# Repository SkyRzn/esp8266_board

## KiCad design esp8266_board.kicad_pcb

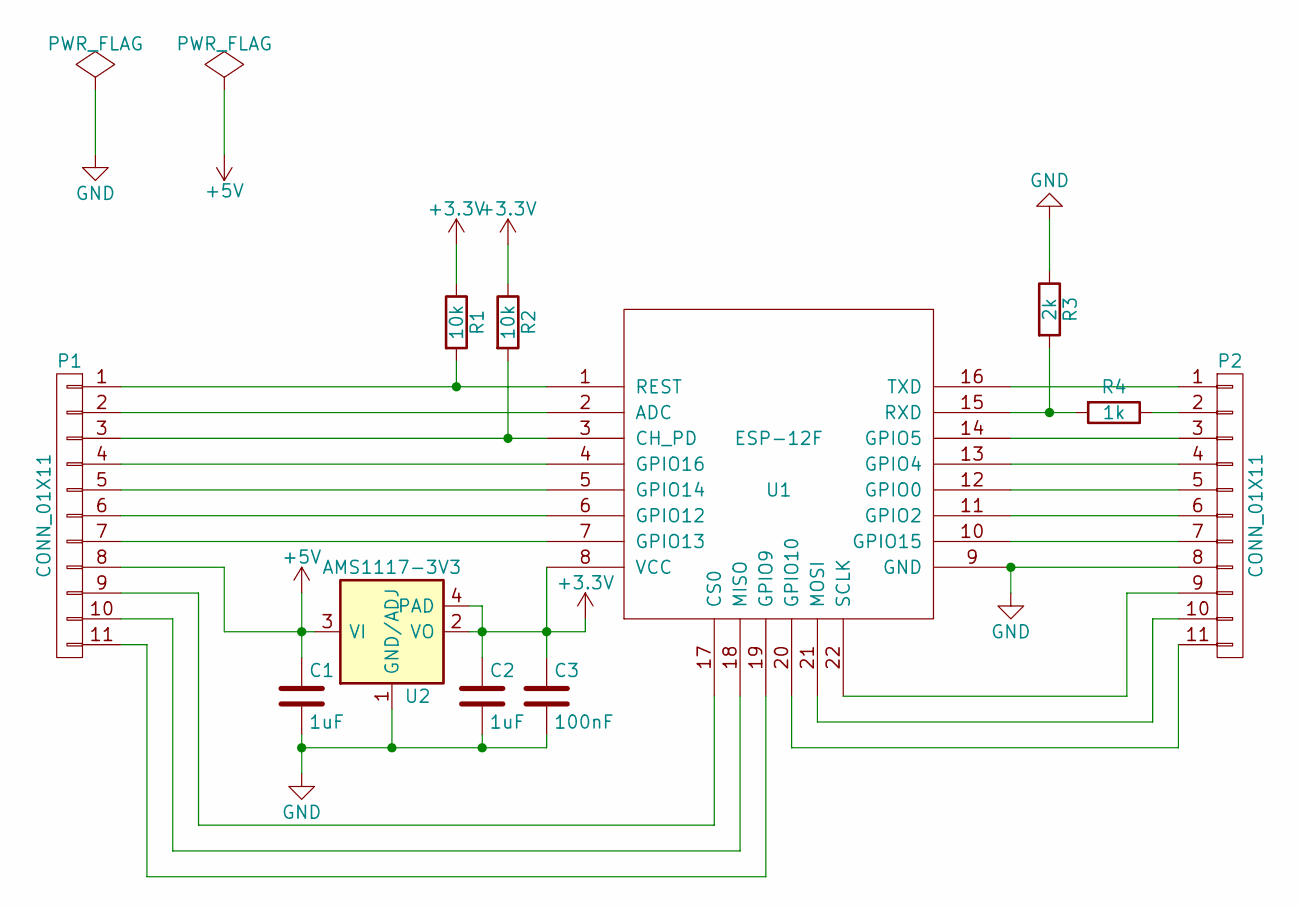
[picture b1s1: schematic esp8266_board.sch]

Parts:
C1, C2: 1uF; C_0805_HandSoldering
C3: 100nF; C_0805_HandSoldering
P1, P2: CONN_01X11; Pin_Header_Straight_1x11
R1, R2: 10k; R_0805_HandSoldering
R3: 2k; R_0805_HandSoldering
R4: 1k; R_0805_HandSoldering
U1: ESP-12F; ESP-12E
U2: AMS1117-3V3; SOT-223; MPN LM1117

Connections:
+3V3: C2.1, C3.1, R1.1, R2.1, U1.8 (VCC), U2.2 (VO), U2.4 (PAD)
+5V: C1.1, P1.8, U2.3 (VI)
GND: C1.2, C2.2, C3.2, P2.8, R3.1, U1.9 (GND), U2.1 (GND/ADJ)
unnamed: P1.1, R1.2, U1.1 (REST)
unnamed: P1.2, U1.2 (ADC)
unnamed: P1.3, R2.2, U1.3 (CH_PD)
unnamed: P1.4, U1.4 (GPIO16)
unnamed: P1.5, U1.5 (GPIO14)
unnamed: P1.6, U1.6 (GPIO12)
unnamed: P1.7, U1.7 (GPIO13)
unnamed: P1.9, U1.17 (CS0)
unnamed: P1.10, U1.18 (MISO)
unnamed: P1.11, U1.19 (GPIO9)
unnamed: P2.1, U1.16 (TXD)
unnamed: P2.2, R4.1
unnamed: P2.3, U1.14 (GPIO5)
unnamed: P2.4, U1.13 (GPIO4)
unnamed: P2.5, U1.12 (GPIO0)
unnamed: P2.6, U1.11 (GPIO2)
unnamed: P2.7, U1.10 (GPIO15)
unnamed: P2.9, U1.22 (SCLK)
unnamed: P2.10, U1.21 (MOSI)
unnamed: P2.11, U1.20 (GPIO10)
unnamed: R3.2, R4.2, U1.15 (RXD)

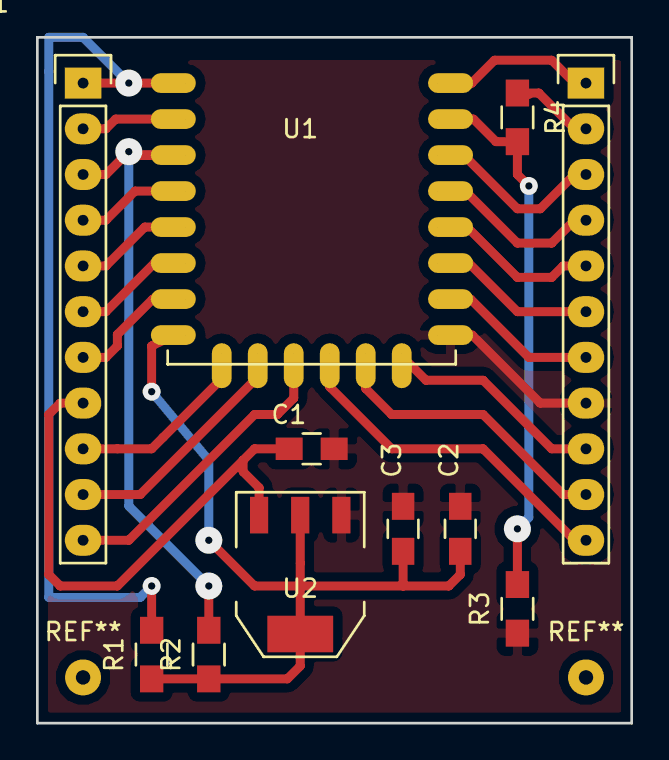
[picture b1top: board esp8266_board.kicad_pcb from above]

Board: 2 copper layers, 33.0 x 38.1 mm, 11 parts (0 on the bottom side), 24 nets.

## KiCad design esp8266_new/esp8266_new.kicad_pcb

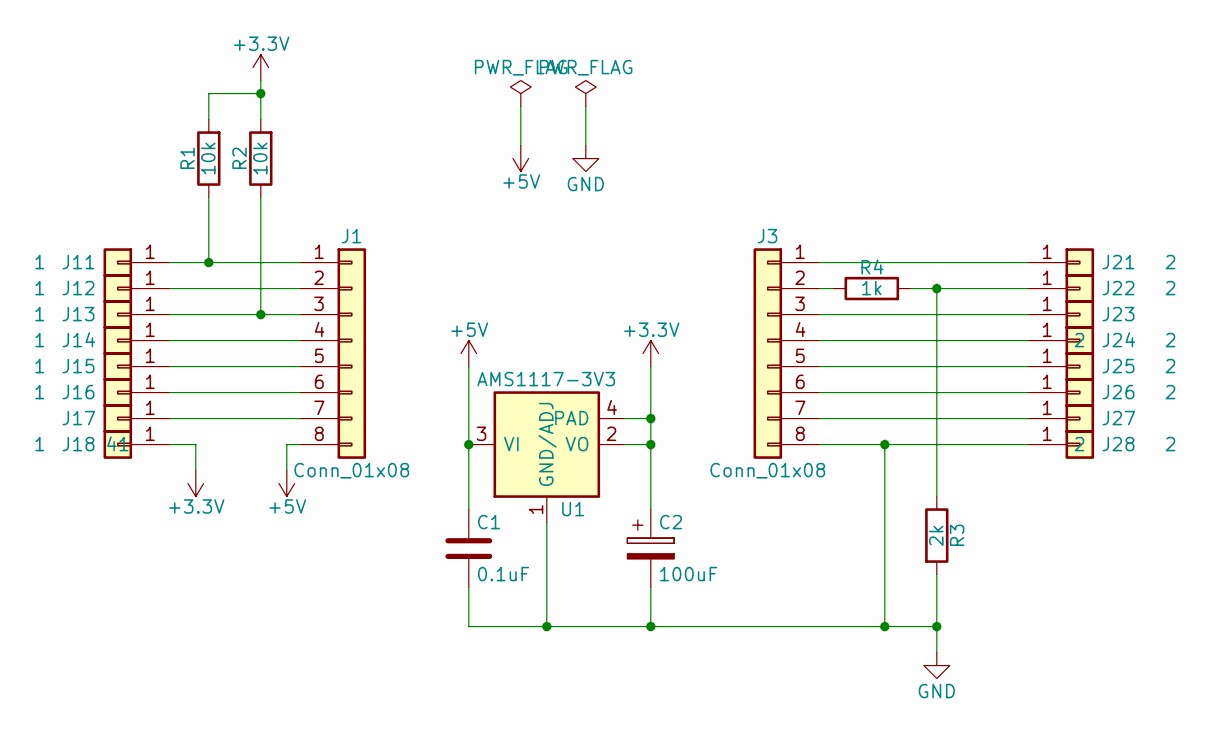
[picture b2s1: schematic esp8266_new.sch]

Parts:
C1: 0.1uF
C2: 100uF
J1, J3: Conn_01x08
J11, J12, J13, J14, J15, J16, J18: 1
J17: 41
J21, J22, J23, J24, J25, J26, J27, J28: 2
R1, R2: 10k
R3: 2k
R4: 1k
U1: AMS1117-3V3; MPN LM1117

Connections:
+3V3: C2.1, J18.1, R1.2, R2.2, U1.2 (VO), U1.4 (PAD)
+5V: C1.1, J1.8, U1.3 (VI)
GND: C1.2, C2.2, J3.8, J28.1, R3.2, U1.1 (GND/ADJ)
unnamed: J1.1, J11.1, R1.1
unnamed: J1.2, J12.1
unnamed: J1.3, J13.1, R2.1
unnamed: J1.4, J14.1
unnamed: J1.5, J15.1
unnamed: J1.6, J16.1
unnamed: J1.7, J17.1
unnamed: J3.2, R4.1
unnamed: J3.1, J21.1
unnamed: J22.1, R3.1, R4.2
unnamed: J3.3, J23.1
unnamed: J3.4, J24.1
unnamed: J3.5, J25.1
unnamed: J3.6, J26.1
unnamed: J3.7, J27.1

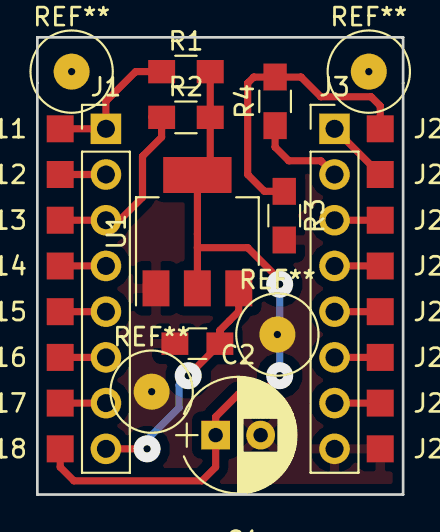
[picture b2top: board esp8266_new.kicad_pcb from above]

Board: 2 copper layers, 20.3 x 25.4 mm, 25 parts (0 on the bottom side), 18 nets.

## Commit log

2018-03-26 Init commit.
2018-04-01 New board.
